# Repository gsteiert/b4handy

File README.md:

# B4Handy
Beeping Blinking Busiiness-card Badge designed for hand assembly

Part of the [Beeping, Blinking Businsess-card Badge (B4) project on Hackaday](https://hackaday.io/project/177897-beeping-blinking-business-card-badge-b4)

This is a full-size, standard business card that can blink and beep with large components and oversized pads for hand assembly.  The back side is completely clear for customization.

You can [order this board at OSH Park](https://oshpark.com/shared_projects/ZGUSlrKn)

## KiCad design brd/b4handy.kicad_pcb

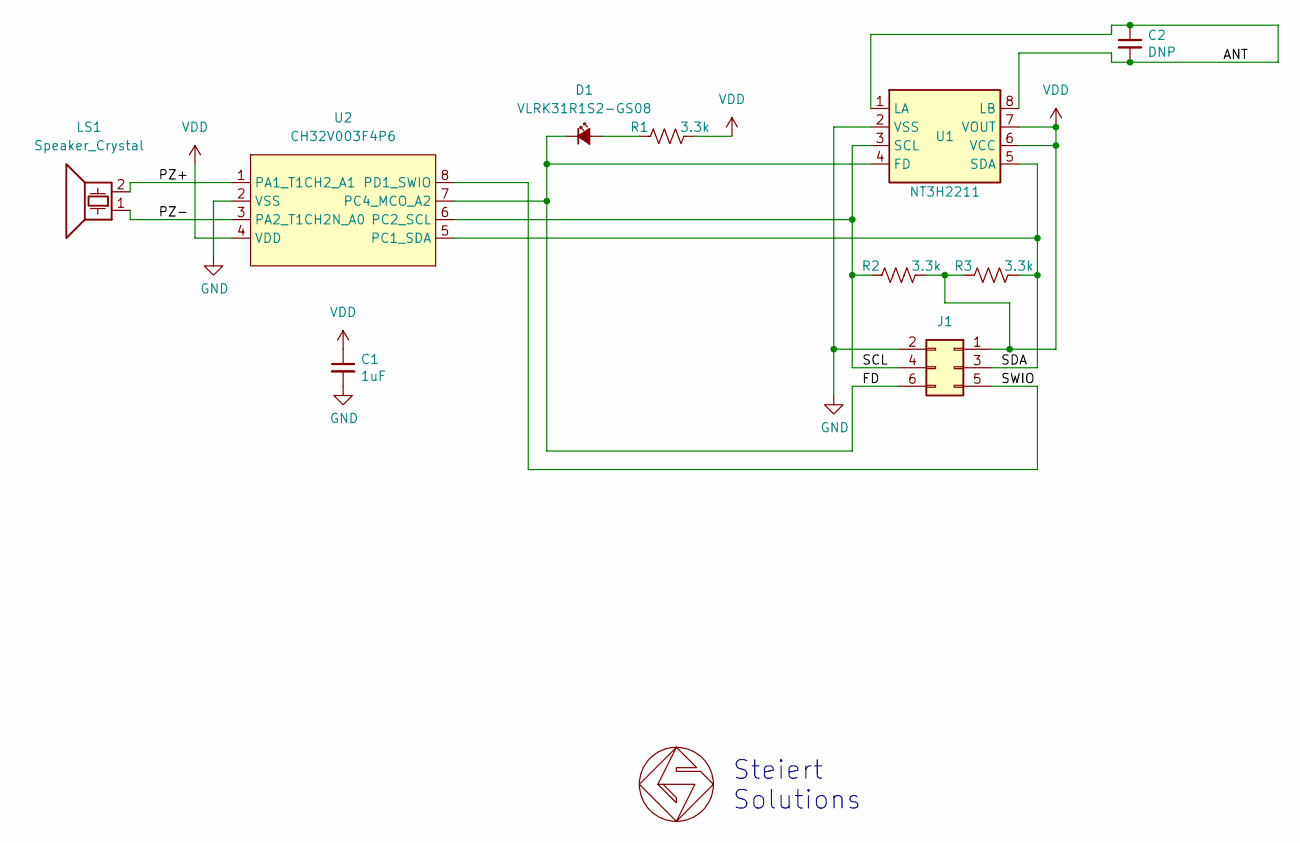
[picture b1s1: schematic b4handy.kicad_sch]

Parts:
C1: 1uF; C_0805_2012Metric_Pad1.18x1.45mm_HandSolder; MPN GCM21BR71H105KA03L; LCSC C126592
C2: DNP; C_0603_1608Metric
D1: VLRK31R1S2-GS08; LED_3228_Reverse_HandSolder; MPN VLRK31R1S2-GS08; LCSC C5346037
GS1: DNP; gs_logo_200mil
J1: DNP; PinHeader_2x03_P2.54mm_Staggered
LS1: Speaker_Crystal; Buzzer_Murata_PKLCS1212E_handy; MPN PKLCS1212E20A0-R1; LCSC C184513
R1, R2, R3: 3.3k; R_0805_2012Metric_Pad1.20x1.40mm_HandSolder; MPN RC0805FR-073K3L; LCSC C114531
U1: NT3H2211; SO-8_3.9x4.9mm_P1.27mm; MPN NT3H2211W0FT1X; LCSC C2654821
U2: CH32V003F4P6; SOP-8_3.9x4.9mm_P1.27mm; MPN CH32V003J4M6; LCSC C5346354

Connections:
/ANT: C2.1, C2.2, U1.1 (LA), U1.8 (LB)
/FD: D1.1 (K), J1.6, U1.4 (FD), U2.7 (PC4_MCO_A2)
/PZ+: LS1.2, U2.1 (PA1_T1CH2_A1)
/PZ-: LS1.1, U2.3 (PA2_T1CH2N_A0)
/SCL: J1.4, R2.2, U1.3 (SCL), U2.6 (PC2_SCL)
/SDA: J1.3, R3.1, U1.5 (SDA), U2.5 (PC1_SDA)
/SWIO: J1.5, U2.8 (PD1_SWIO)
GND: C1.2, J1.2, U1.2 (VSS), U2.2 (VSS)
unnamed: D1.2 (A), R1.2
VDD: C1.1, J1.1, R1.1, R2.1, R3.2, U1.6 (VCC), U1.7 (VOUT), U2.4 (VDD)

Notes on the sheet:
Steiert Solutions

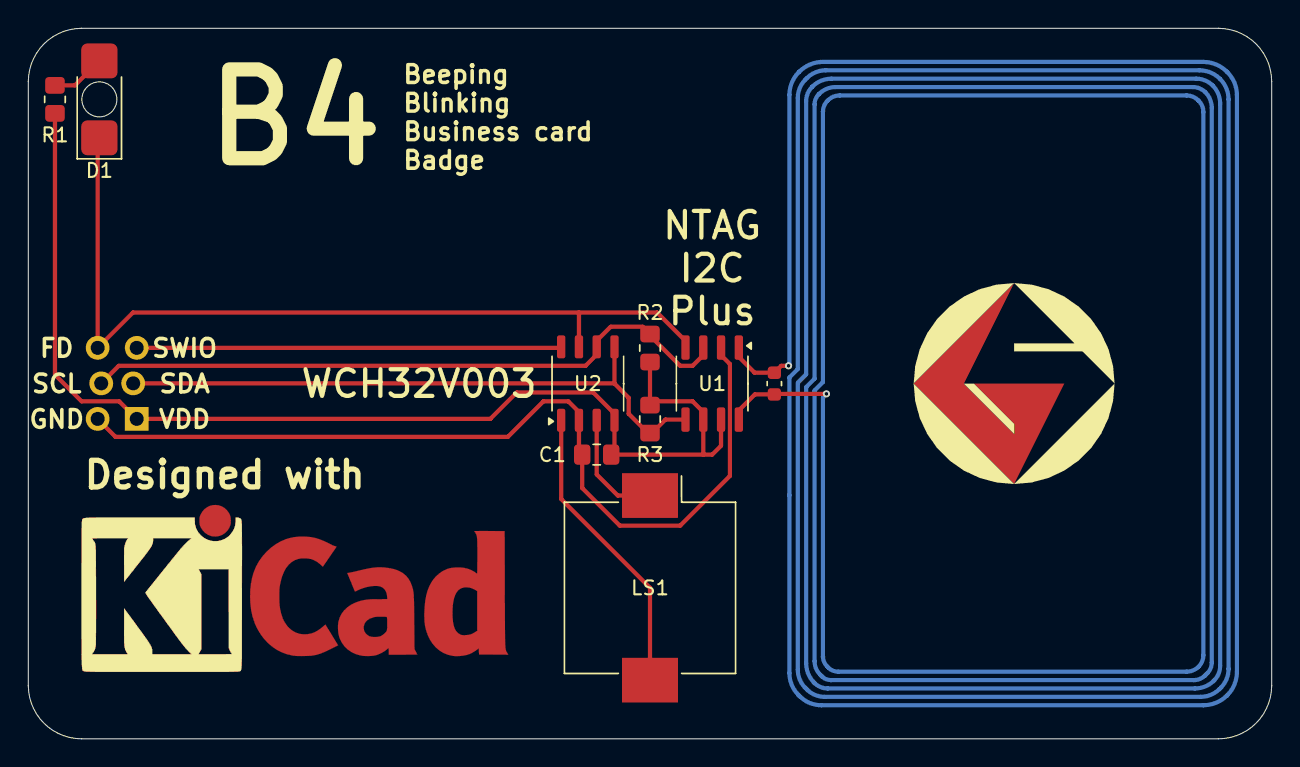
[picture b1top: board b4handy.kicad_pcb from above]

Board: 2 copper layers, 88.9 x 50.8 mm, 10 parts (0 on the bottom side), 10 nets.

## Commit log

2024-05-26 adding completed board design and updated README
